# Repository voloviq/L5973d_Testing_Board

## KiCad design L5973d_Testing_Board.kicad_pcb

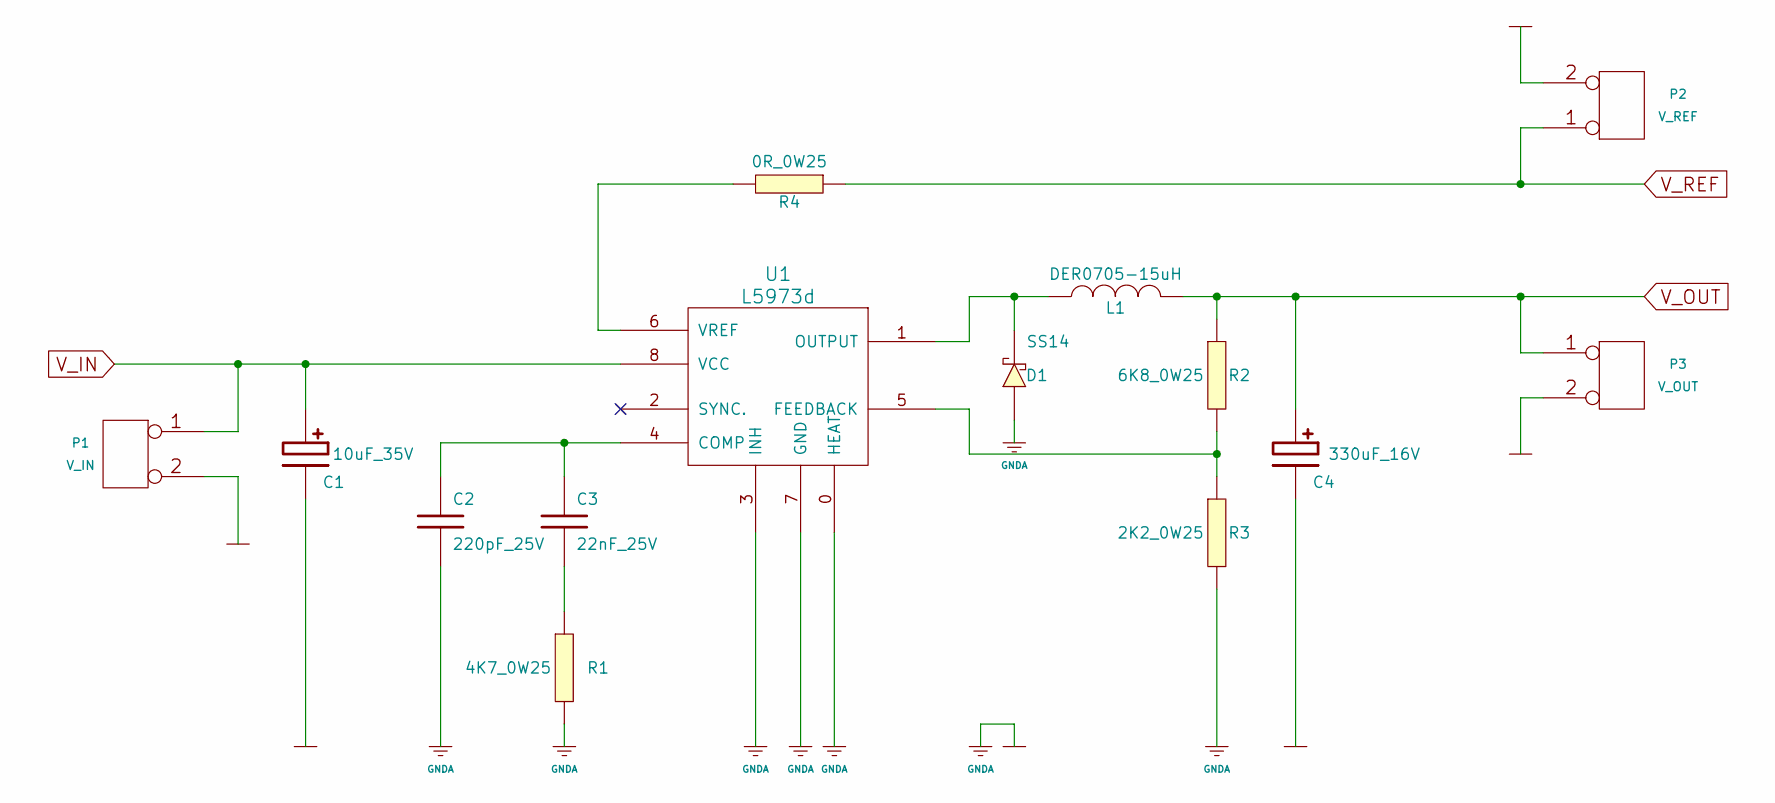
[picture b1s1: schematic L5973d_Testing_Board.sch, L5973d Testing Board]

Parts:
C1: 10uF_35V; 10uF_10V_Size_C_5x5_3
C2: 220pF_25V; 27pF_25V_SM0805
C3: 22nF_25V; 27pF_25V_SM0805
C4: 330uF_16V; 330uF_16V_Size_F_8x8_3
D1: SS14; SS14_SMD_DO21AC
L1: DER0705-15uH
P1: V_IN; mors_2p
P2: V_REF; mors_2p
P3: V_OUT; mors_2p
R1: 4K7_0W25; 4k7_0W25_SM0805
R2: 6K8_0W25; 6k8_0W25_SM0805
R3: 2K2_0W25; 2k2_0W25_SM0805
R4: 0R_0W25; 0R_0W25_SM0805
U1: L5973d; L5973d_SO8

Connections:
GNDA: C1.2, C2.2, C4.2, D1.1 (A), P1.2 (PM), P2.2 (PM), P3.2 (PM), R1.2, R3.2, U1.0 (HEAT), U1.3 (INH), U1.7 (GND)
unnamed: C2.1, C3.1, U1.4 (COMP)
unnamed: C3.2, R1.1
unnamed: D1.2 (K), L1.1, U1.1 (OUTPUT)
unnamed: R2.2, R3.1, U1.5 (FEEDBACK)
unnamed: R4.2, U1.6 (VREF)
V_IN: C1.1, P1.1, U1.8 (VCC)
V_OUT: C4.1, L1.2, P3.1, R2.1
V_REF: P2.1, R4.1

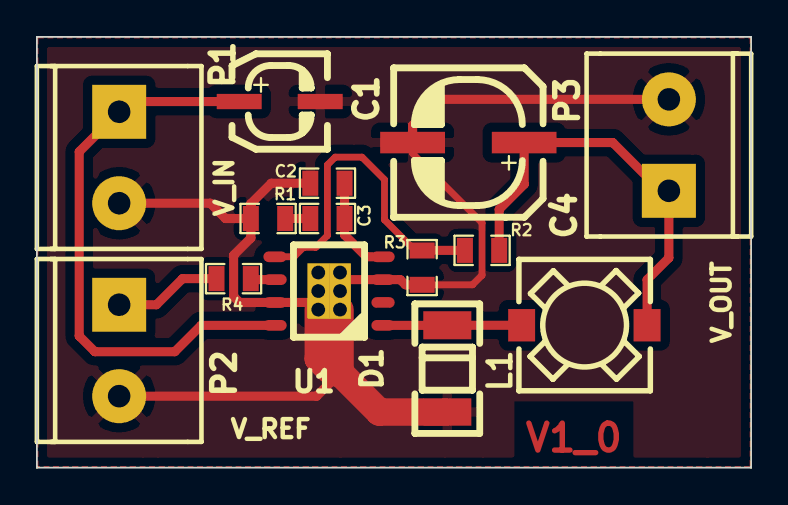
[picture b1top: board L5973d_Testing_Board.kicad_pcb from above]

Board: 2 copper layers, 39.7 x 23.9 mm, 14 parts (0 on the bottom side), 9 nets.

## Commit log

2015-04-27 Initial Testing Board for L5973d
